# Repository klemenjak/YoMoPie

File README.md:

# Servus!

Computational methods for the enhancement of energy efficiency rely on a measurement process with sufficient accuracy and number of measurements. Networked energy meters, energy monitors, serve as a vital link between the energy consumption of households and key insights that reveal strategies to achieve significant energy savings.
With YoMoPie, we propose a user-oriented energy monitor for the Raspberry Pi platform that aims to enable intelligent energy services in households. YoMoPie measures active as well as apparent power, stores data locally, and integrates a user-friendly Python library. Furthermore, the presented energy monitor allows users to run self-designed services in their home to enhance energy efficiency. Potential services are (but not limited to) residential demand response, immediate user feedback, smart meter data analytics, or energy disaggregation.

<!--- YoMoPie builds on [the work published in [1]](https://link.springer.com/article/10.1007%2Fs00450-014-0290-8#/page-1).
YoMoPie provides the following advancements:

* It doesn't suffer from a data update rate of 1 second
* It stores data locally
* It integrates a new measurement IC that allows poly-phase metering
* It builds on the Raspberry platform
* The YoMoPie Python package enables easy handling -->

## Research Paper on YomoPie

All design files and pieces of software are available free of charge. However, in case you use the PCB design, code, or other material for research purposes, we kindly ask you to cite our peer-reviewed research paper:

* *Title*: YoMoPie: A User-Oriented Energy Monitor to Enhance Energy Efficiency in Households
* *Authors*: Mr. Christoph Klemenjak, Mr. Stefan Jost and Dr. Wilfried Elmenreich
* *Conference*: 2018 IEEE Conference on Technologies for Sustainability (SusTech)

Recommended Citation:
```
@INPROCEEDINGS{klemenjak2018yomopie,
author={C. Klemenjak and S. Jost and W. Elmenreich},
booktitle={2018 IEEE Conference on Technologies for Sustainability (SusTech)},
title={Yo{M}o{P}ie: {A} User-Oriented Energy Monitor to Enhance Energy Efficiency in Households},
year={2018},
volume={},
number={},
pages={},
keywords={},
doi={},
ISSN={},
month={Nov}}
```

|                 | YoMoPie  |
| ------------- | -----:|
|Communication|  WiFi, Ethernet, RF |
|Measurement|  P, Q, S, I, U |
|Number of connections| 1 or 3 |
|Integrated relay |  yes |
|Sampling frequency|  tba. |
|Data update rate |  tba. |
|Power calculation|  Hardware |
|Open-Source|  yes |
|RaspberryPi-compatible|  yes  |
|Costs| approx. 50€  |

Beside a current and a voltage sensor, the board integrates an energy metering chip, the ADE7754. Our library is designed in a way to offer single-phase as well as multi-phase metering.

## Installation

The YoMoPie Python package is available on Python Package Index (PyPI), a repository of software for the Python programming language, and can be installed by issuing one command:

```python
pip3 install YoMoPie
```
Additionally, the entire source code and a manual can be obtained from our YoMoPie Github repository.

## Examples of use

After a successful installation process, the YoMoPie package is available system-wide and can be accessed by a simple import command:
```python
import YoMoPie as yomopie
yp = yomopie.YoMoPie()
```

During initialisation, the number of line conductors has to be set (single or polyphase metering):
```python
yomo.set_lines(1)
```

To test the operation, we recommend to call the function *do_n_measurements*. Based on the number of samples and the sampling period, the function will return first measurement values and saves it into the target file:
```python
yomo.do_n_measurements(number of samples, sampling period, target file)
```

Active power, apparent power, current, and voltage samples can be read with commands such as:
```python
[t, I] = yp.get_irms()
[t, U] = yp.get_vrms()
[t, P] = yp.get_active_energy()
[t, S] = yp.get_apparent_energy()
```
In the same vein, users can activate continuous data logging or perform a fixed amount of subsequent measurements:
```python
yp.do_metering()
yp.do_n_measurements(quantity, rate, file)
```

The operational mode (OPMODE) register defines the general configuration of the integrated measurement chip ADE7754. By writing to this register, A/D converters can be turned on/off, sleep mode can be activated, or a software chip reset can be triggered. For further information, we refer to the datasheet of the measurement chip.

```python
yp.set_operational_mode(OPMODE)
```

# YoMoPie Python package documentation
**[Imports](#imports)**<br>
**[Classvariables](#classvariables)**<br>
**[Methods](#methods)**<br>
*[-init](#init)*<br>
*[-init_yomopie](#init_yomopie)*<br>
*[-set_lines](#set_lines)*<br>
*[-enable_board](#enable_board)*<br>
*[-disable_board](#disable_board)*<br>
*[-chip_reset](#chip_reset)*<br>
*[-write_8bit](#write_8bit)*<br>
*[-read_8bit](#read_8bit)*<br>
*[-write_16bit](#write_16bit)*<br>
*[-read_16bit](#read_16bit)*<br>
*[-read_24bit](#read_24bit)*<br>
*[-get_temp](#get_temp)*<br>
*[-get_laenergy](#get_laenergy)*<br>
*[-get_lappenergy](#get_lappenergy)*<br>
*[-get_period](#get_period)*<br>
*[-set_operational_mode](#set_operational_mode)*<br>
*[-set_measurement_mode](#set_measurement_mode)*<br>
*[-close_SPI_connection](#close_SPI_connection)*<br>
*[-get_aenergy](#get_aenergy)*<br>
*[-get_active_energy](#get_active_energy)*<br>
*[-get_apparent_energy](#get_apparent_energy)*<br>
*[-get_sample](#get_sample)*<br>
*[-get_sampleperperiod](#get_sampleperperiod)*<br>
*[-get_vrms](#get_vrms)*<br>
*[-get_irms](#get_irms)*<br>
*[-do_n_measurements](#do_n_measurements)*<br>
*[-do_metering](#do_metering)*<br>
*[-change_factors](#change_factors)*<br>
*[-reset_factors](#reset_factors)*<br>
*[-init_nrf24](#init_nrf24)*<br>
*[-write_nrf24](#write_nrf24)*<br>
*[-read_nrf24](#read_nrf24)*<br>
**[OPMODE](#opmode)**<br>
**[MMODE](#mmode)**<br>

## Imports
YomoPie requires some additional libraries:

**time**: The time package is required to obtain timestamps.

**math**: YoMoPie requires the math lib for calculations such as reactive energy.

**spidev**: The YoMoPie integrates an energy monitor IC, which communicates via SPI to the RPi. To enable this communication, YoMoPie exploits the spidev lib.

**sys**: This module provides access to some variables used or maintained by the interpreter and to functions that interact strongly with the interpreter.

**RPi.GPIO**: In order to allow further extensions of the YoMoPie eco-system, our package integrates the RPi.GPIO. Also, the reset pin is controlled via GPIO.

**NRF24**: This package allows to utilize the RF module for 2.4 GHz communication.

```python
import time
import math
import spidev
import sys
import RPi.GPIO as GPIO
from lib_nrf24 import NRF24
```
## Class variables

To correctly access the internal registers of the energy monitor IC, several custom variables are required to adjust the register values.

* **read** and **write**: These variables hold the mask that defines the operational mode. Therefore, for reading a register the given address and the **read** variable are the inputs of a bitwise AND operation. On the other hand, for writing to a register the register address and the **write** variable are the inputs of a bitwise OR operation.

* **spi**, **active_lines** and **debug**: These variables hold the SPI object, save the number of active lines, and enable/disable the debug mode.

* **radio**: This object will be used for the RF communication and its functions.
* **sample interval** and **max_f_sample**: defines the time between two samples (with respect to the start_sampling method) in seconds and the maximum sampling frequency (with respect to the sampling error).
* **active_power_LSB**, **apparent_power_LSB**, **vrms_factor** and **irms_factor**: Convert register values to physical quantities and represent permanent conversion factors.

```python
read = 0b00111111
write = 0b10000000
spi=0
radio=0
active_lines = 1
debug = 1

sample_intervall = 1
max_f_sample = 10

active_power_LSB= 0.000013292
apparent_power_LSB= 0.00001024
vrms_factor = 0.000047159
irms_factor = 0.000010807
```

## Methods

In this Section, we describe every method of our  package. A description of function parameters and return values is given.

### __init__

**Description**: This method represents  the constructor and creates a new YoMoPie object.

**Parameters**: None.

**Returns**: Nothing.

```python
def __init__(self):
	self.spi=spidev.SpiDev()
	self.init_yomopie()
	return
```

### init_yomopie

**Description**: Initialises the YoMoPie object. Sets the GPIO mode, disables GPIO warnings and defines pin 19 as output. Also opens a new SPI connection via the SPI device (0,0), sets the SPI speed to 62500 Hz and sets the SPI mode to 1. Finally, the function set_lines is called to set the MMODE, WATMODE and VAMODE.

**Parameters**: None.

**Returns**: Nothing.

```python
def init_yomopie(self):
	GPIO.setmode(GPIO.BCM)
	GPIO.setwarnings(False)
	GPIO.setup(19,GPIO.OUT)
	self.spi.open(0,0)
	self.spi.max_speed_hz = 62500
	self.spi.mode = 0b01
	self.set_lines(self.active_lines)
	self.sampleintervall = 1
	return
```

### set_lines

**Description**: This function sets the number of active phases that will be measured.

**Parameters**:
* lines - Number of phases

**Returns**: Nothing.

```python
def set_lines(self, lines):
	if (lines != 1) and (lines != 3):
		print("Incompatible number of power lines")
		return
	else:
		self.active_lines = lines
		if self.active_lines == 3:
			self.write_8bit(0x0D, 0x3F)
			self.write_8bit(0x0E, 0x3F)
			self.set_measurement_mode(0x70)
		elif self.active_lines == 1:
			self.write_8bit(0x0E, 0x24)
			self.set_measurement_mode(0x10)
			self.write_8bit(0x0D, 0x24)
		return
```

### enable_board

**Description**: Enables the board by pulling pin 19 to HIGH.

**Parameters**: None.

**Returns**: Nothing.

```python
def enable_board(self):
	GPIO.output(19, GPIO.HIGH)
	return
```

### disable_board

**Description**: Disables the board by pulling pin 19 to LOW.

**Parameters**: None.

**Returns**: Nothing.

```python
def disable_board(self):
	GPIO.output(19, GPIO.LOW)
	return
```

### chip_reset

**Description**: Resets the chip to the manufacturer settings

**Parameters**: None.

**Returns**: Nothing.

```python
def chip_reset(self):
	self.write_8bit(0x0A, 0x40)
	time.sleep(1);
	return
```		
### write_8bit    

**Description**: Writes 8 bit to the given address.

**Parameters**:

* register - 8 bit address of the register (see ADE7754 register table)

* value - 8 bit of value that will be written into the register

**Returns**: Nothing.

```python
def write_8bit(self, register, value):
	self.enable_board()
	register = register | self.write
	self.spi.xfer2([register, value])
	return
```

### read_8bit

**Description**: Reads 8 bit of data from the given address.

**Parameters**:
* register - 8 bit address of the register (see ADE7754 register table)

**Returns**: the 8 bit of data in the register as decimal

```python
def read_8bit(self, register):
	self.enable_board()
	register = register & self.read
	result = self.spi.xfer2([register, 0x00])[1:]        
	return result[0]
```

### write_16bit

**Description**: Writes 16 bit to the given address.

**Parameters**:

* register - 8 bit address of the register (see ADE7754 register table)

* value - 16 bit of value that will be written into the register

**Returns**: Nothing.

```python
def write_16bit(self, register, value):
	self.enable_board()
	register = register | self.write
	self.spi.xfer2([register, value[0], value[1]])
	return
```		

### read_16bit  

**Description**: Reads 16 bit of data from the given address.

**Parameters**:
* register - 8 bit address of the register (see ADE7754 register table)

**Returns**: the 16 bit of data in the register as decimal

```python
def read_16bit(self, register):
	self.enable_board()
	register = register & self.read
	result = self.spi.xfer2([register, 0x00, 0x00])[1:]
	dec_result = (result[0]<<8)+result[1]
	return dec_result
```

### read_24bit        

**Description**: Reads 24 bit of data from the given address.

**Parameters**:
* register - 8 bit address of the register (see ADE7754 register table)

**Returns**: the 24 bit of data in the register as decimal

```python
def read_24bit(self, register):
	self.enable_board()
	register = register & self.read
	result = self.spi.xfer2([register, 0x00, 0x00, 0x00])[1:]
	dec_result = (result[0]<<16)+(result[1]<<8)+(result[2])
	return dec_result
```

### get_temp

**Description**: Reads the temperature register (0x08).

**Parameters**: None.

**Returns**: A list [timestamp, temperature in °C]

```python
def get_temp(self):
	reg = self.read_8bit(0x08)
	temp = [time.time(),(reg-129)/4]
	return temp
```

### get_laenergy

**Description**: Reads the active energy register (0x03).

**Parameters**: None.

**Returns**: A list [timestamp, value of the register]

```python
def get_laenergy(self):
	laenergy = [time.time(), self.read_24bit(0x03)]
	return laenergy
```

### get_lappenergy

**Description**: Reads the apparent energy register (0x06).

**Parameters**: None.

**Returns**: A list [timestamp, value of the register]

```python
def get_lappenergy(self):
	lappenergy = [time.time(), self.read_24bit(0x06)]
	return lappenergy
```

### get_period   

**Description**: Reads the period register (0x07).

**Parameters**: None.

**Returns**: A list [timestamp, value of the register]

```python
def get_period(self):
       period = [time.time(), self.read_16bit(0x07)]
       return period
```

### set_operational_mode

**Description**: Sets the OPMODE. For more information see section OPMODE.

**Parameters**:
* value - 8 bit of data representing the OPMODE

**Returns**: Nothing.

```python
def set_operational_mode(self, value):
	self.write_8bit(0x0A, value)
	return
```

### set_measurement_mode

**Description**: Sets the MMODE. For more information see section MMODE.

**Parameters**:
* value - 8 bit of data representing the MMODE

**Returns**: Nothing.

```python
def set_measurement_mode(self, value):
	self.write_8bit(0x0B, value)
	return
```

### close_SPI_connection

**Description**: Closes the SPI connection.

**Parameters**: None.

Returns**: 0 if connection is closed.

```python
def close_SPI_connection(self):
	self.spi.close()
	return 0
```
### get_aenergy

**Description**: Reads the active energy register (0x01).

**Parameters**: None.

**Returns**: A list [timestamp, value of register converted to real value]

```python
def get_aenergy(self):
	aenergy = [time.time(), self.active_power_LSB * self.read_24bit(0x01) *  3600/self.sample_intervall]
	return aenergy
```
### get_active_energy

**Description**: Reads the active energy register (0x02) and resets the register value.

**Parameters**: None.

**Returns**: A list [timestamp, value of register converted to real value]

```python
def get_active_energy(self):
	aenergy =  [time.time(), self.active_power_LSB * self.read_24bit(0x02) *  3600/self.sample_intervall]
	return aenergy
```
### get_apparent_energy

**Description**: Reads the apparent energy register (0x05) and resets the register vlaue.

**Parameters**: None.

**Returns**: A list [timestamp, value of register converted to real value]

```python
def get_apparent_energy(self):
	appenergy = [time.time(), self.apparent_power_LSB * self.read_24bit(0x05)*  3600/self.sample_intervall]
	return appenergy
```
### get_sample

**Description**: Takes one sample and calculates the active energy, apparent energy, reactive energy, VRMS and IRMS.

**Parameters**: None.

**Returns**: A list of 7 elements [timestamp, active energy, apparent energy, reactive energy, period, VRMS, IRMS]

```python
def get_sample(self):
	aenergy = self.get_aenergy()[1] *self.active_factor
	appenergy = self.get_appenergy()[1] *self.apparent_factor
	renergy = math.sqrt(appenergy*appenergy - aenergy*aenergy)
	if self.debug:
		print"Active energy: %f W, Apparent energy: %f VA, Reactive Energy: %f var" %(aenergy, appenergy, renergy)
		print"VRMS: %f IRMS: %f" %(self.get_vrms()[1]*self.vrms_factor,self.get_irms()[1]*self.irms_factor)
	sample = []
	sample.append(time.time())
	sample.append(aenergy)
	sample.append(appenergy)
	sample.append(renergy)
	sample.append(self.get_period()[1])
	sample.append(self.get_vrms()[1]*self.vrms_factor)
	sample.append(self.get_irms()[1]*self.irms_factor)
	return sample
```

### get_vrms

**Description**: Reads the VRMS register depending.

**Parameters**: None.

**Returns**: A list of 2 elements [timestamp, Phase A VRMS] or 4 elements [timestamp, Phase A VRMS, Phase B VRMS, Phase C VRMS]

```python
def get_vrms(self):
	if self.active_lines == 1:
		avrms = [time.time(), self.read_24bit(0x2C)]
		return avrms
	elif self.active_lines == 3:
		vrms = []
		vrms.append(time.time())
		vrms.append(self.read_24bit(0x2C))
		vrms.append(self.read_24bit(0x2D))
		vrms.append(self.read_24bit(0x2E))
		return vrms
	return 0
```

### get_irms

**Description**: Reads the IRMS register.

**Parameters**: None.

**Returns**: A list of 2 elements [timestamp, Phase A IRMS] or 4 elements [timestamp, Phase A IRMS, Phase B IRMS, Phase C IRMS]

```python
def get_irms(self):
	if self.active_lines == 1:
		airms = [time.time(), self.read_24bit(0x29)]
		return airms
	elif self.active_lines == 3:
		irms = []
		irms.append(time.time())
		irms.append(self.read_24bit(0x29))
		irms.append(self.read_24bit(0x2A))
		irms.append(self.read_24bit(0x2B))
		return vrms
	return 0
```

### get_sampleperperiod

**Description**: Reads multiple register and returns the values adjusted to the sampling frequency. This function will be used in the do_n_measurements
 function.

**Parameters**:
* samplerate - the actual samplerate

**Returns**: A list of 7 elements [timestamp, active energy, apparent energy, reactive energy, period, VRMS, IRMS]

```python
def get_sampleperperiod(self, samplerate):
	aenergy = self.get_aenergy()[1] *self.active_factor * 3600/samplerate
	appenergy = self.get_appenergy()[1] *self.apparent_factor * 3600/samplerate
	renergy = math.sqrt(abs(appenergy*appenergy - aenergy*aenergy))
	vrms = self.get_vrms()[1]*self.vrms_factor
	irms = self.get_irms()[1]*self.irms_factor
	if self.debug:
		print("Active energy: %f W, Apparent energy: %f VA, Reactive Energy: %f var" % (aenergy, appenergy, renergy))
		print("VRMS: %f IRMS: %f" %(vrms,irms))
	sample = []
	sample.append(time.time())
	sample.append(aenergy)
	sample.append(appenergy)
	sample.append(renergy)
	sample.append(self.get_period()[1])
	sample.append(vrms)
	sample.append(irms)
	return sample
```

### do_n_measurements

**Description**: Takes *nr_samples* with sampling period *samplerate* and saves the measurements into the give file.

**Parameters**:

* nr_samples - this are the number of samples that will be taken, integer greater then 0
* samplerate - this is the time between each sample, integer greater then 0
* file - this will be the path and name of the file, where the date will be stored

**Returns**: A list of samples (each sample is a list of 7 elements)

```python
def do_n_measurements(self, nr_samples, samplerate, file):
	if (samplerate<1) or (nr_samples<1):
		return 0
	self.sample_intervall = samplerate
	samples = []
	for i in range(0, nr_samples):
		for j in range(0, samplerate):
			time.sleep(1)
	sample = self.get_sampleperperiod(samplerate)
	samples.append(sample)
	logfile = open(file, "a")
	for value in sample:
		logfile.write("%s; " % value)
	logfile.write("\n")
	logfile.close()
	return samples
```

### do_metering

**Description**: Starts a sampling process and saves the data into a file.

**Parameters**:

* f_sample - the sampling frequency (<= 10, but if max_f_sample is changed, this value can be up to 100 with a higher error)
* file - this will be the path and name of the file, where the date will be stored. If this parameter is empty the data will be stored in "smart_meter_output.csv".

**Returns**: Nothing.

```python
def do_metering(self, f_sample, file):
	if (f_sample > max_f_sample):
		print('Incompatible sampling frequency!')
		return 1
	if (file == ''):
		file = 'smart_meter_output.csv'
	for i in range(0,86400):
		sample = []
		sample.append(time.time())
		sample.append(i)
		sample.append(self.get_active_energy())
		sample.append(self.get_apparent_energy())
		data_file = open(file,'a')
		for value in sample:
			logfile.write("%s; " % value)
		logfile.write("\n")
		##print(sample)
		time.sleep(1/f_sample);
	return 0
```

### change_factors

**Description**: Changes the multiplication factors for the register values.

**Parameters**:

* active_f - this is the factor for the active energy calculation
* apparent_f - this is the factor for the apparent energy calculation
* vrms_f - this is the factor for the vrms calculation
* irms_f  this is the factor for the irms calculation

**Returns**: Nothing.

```python
def change_factors(self, active_f, apparent_f, vrms_f, irms_f):
	self.active_power_LSB = active_f
	self.apparent_power_LSB = apparent_f
	self.vrms_factor = vrms_f
	self.irms_factor = irms_f
	return
```

### reset_factors

**Description**: Resets the multiplication factors to the default values. The default values are calculated by our measurements with calibrated equipment.

**Parameters**: None.

**Returns**: Nothing.

```python
def reset_factors(self):
	self.active_power_LSB= 0.000013292
	self.apparent_power_LSB= 0.00001024
	self.vrms_factor = 0.000047159
	self.irms_factor = 0.000010807
	return
```

### init_nrf24

**Description**: Initializes the RF communication via the NRF24 chip.

**Parameters**: None.

**Returns**: Nothing.

```python
def init_nrf24(self):
	pipes = [[0xe7, 0xe7, 0xe7, 0xe7, 0xe7], [0xc2, 0xc2, 0xc2, 0xc2, 0xc2]]

	self.radio = NRF24(GPIO, self.spi)
	self.radio.begin(1, 13)
	self.radio.setPayloadSize(32)
	self.radio.setChannel(0x60)

	self.radio.setDataRate(NRF24.BR_2MBPS)
	self.radio.setPALevel(NRF24.PA_MIN)
	self.radio.setAutoAck(True)
	self.radio.enableDynamicPayloads()
	self.radio.enableAckPayload()
	self.radio.openWritingPipe(pipes[1])
	self.radio.openReadingPipe(1, pipes[0])
	self.radio.printDetails()
	return
```

### write_nrf24

**Description**: Sends a message via the RF communication.

**Parameters**:
* command - the message that will be written via RF

**Returns**: Nothing.

```python
def write_nrf24(self, command):
	message = []
	message = list(command)
	self.radio.write(message)
	print("Send: {}".format(message))

	if self.radio.isAckPayloadAvailable():
		pl_buffer = []
		self.radio.read(pl_buffer, self.radio.getDynamicPayloadSize())
		print(pl_buffer)
		print("Translating the acknowledgment to unicode chars...")
		string = ""
		for n in pl_buffer:
			if(n >= 32 and n <= 126):
			string += chr(n)
		print(string)
	return
```

### read_nrf24

**Description**: Reads a message via the RF communication.

**Parameters**: None.

**Returns**: Nothing.

```python
def read_nrf24(self):
	print("Ready to receive data...")
	self.radio.startListening()
	pipe = [0]
	while not self.radio.available(pipe):
		time.sleep(1/100)
	receivedMessage = []
	self.radio.read(receivedMessage, self.radio.getDynamicPayloadSize())

	print("Translating the receivedMessage to unicode chars...")
	string = ""
	for n in receivedMessage:
		if (n >= 32 and n <= 126):
			string += chr(n)
		print("Our sensor sent us: {}".format(string))
	self.radio.stopListening()
	return
```
## OPMODE
The operational mode (OPMODE) register defines the general configuration of the ADE7754 chip. For detailed information about the individual bits of this register we refer to [Table IX](https://github.com/klemenjak/YoMoPie/blob/master/Datasheets/ADE7754.pdf).

## MMODE
The configuration of period and peak measurements are defined by writing to the MMODE register (0x0B). For more information about the register we refer to [Table XII](https://github.com/klemenjak/YoMoPie/blob/master/Datasheets/ADE7754.pdf).

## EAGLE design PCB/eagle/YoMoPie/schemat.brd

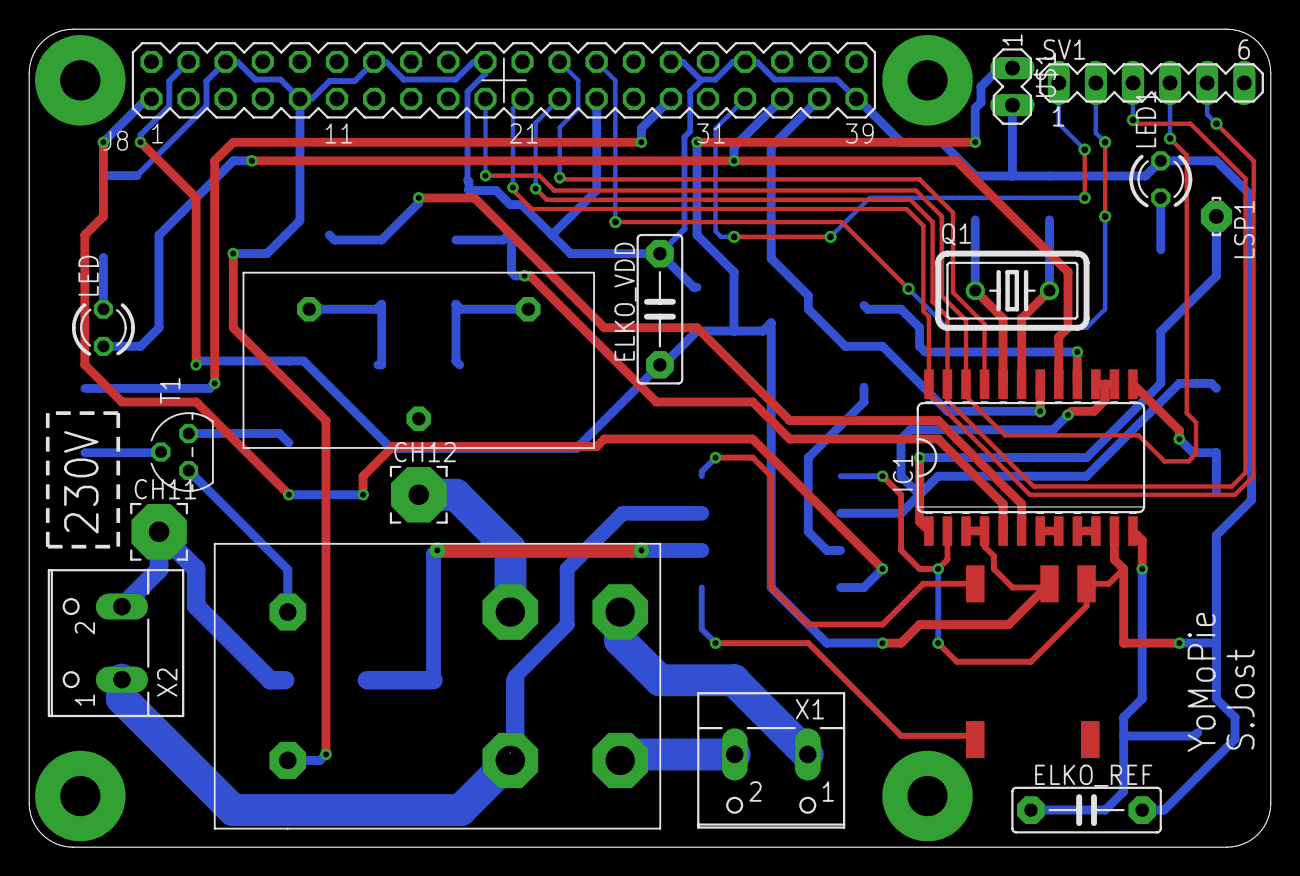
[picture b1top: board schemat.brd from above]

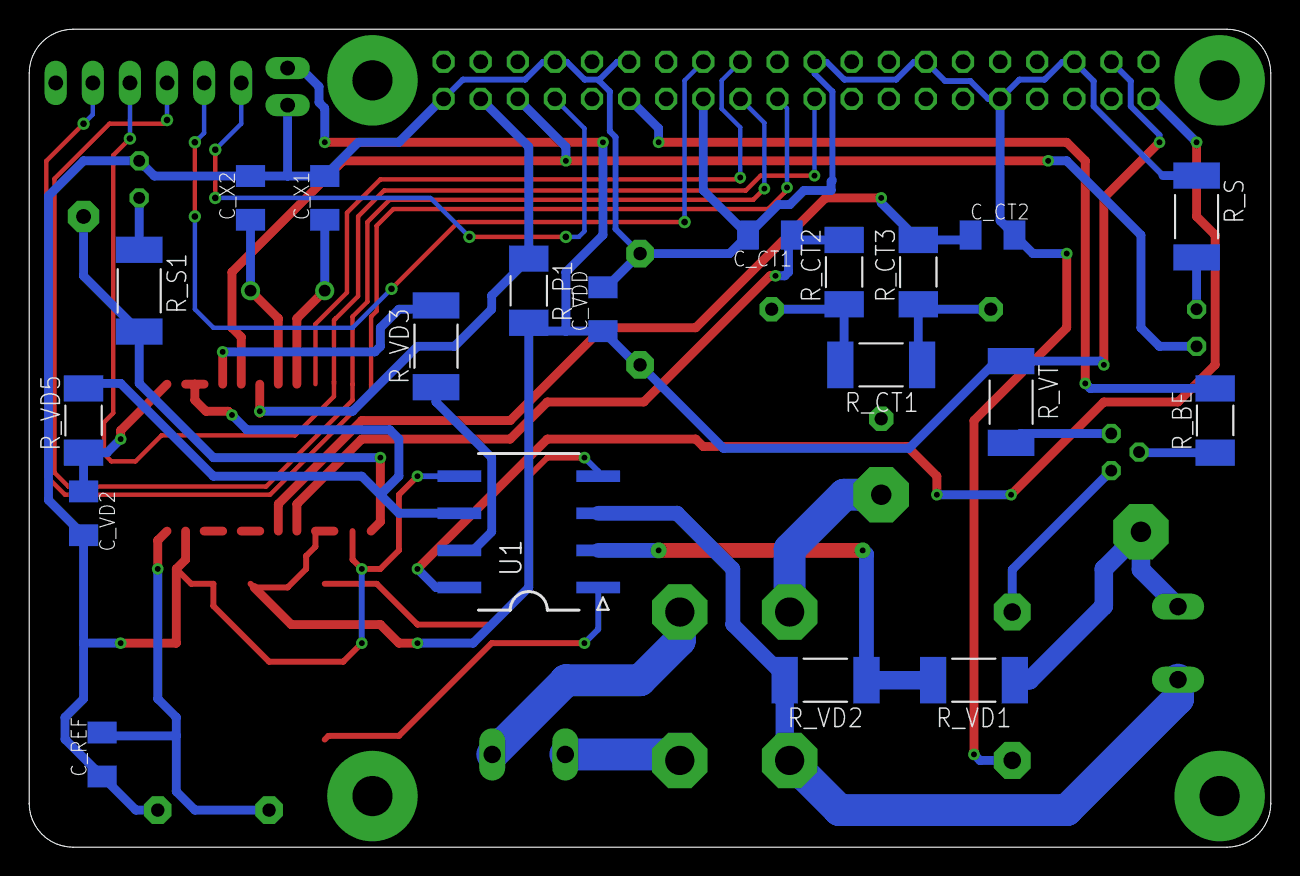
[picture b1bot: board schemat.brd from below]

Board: 2 copper layers, 85.0 x 56.0 mm, 38 parts (20 on the bottom side), 39 nets.

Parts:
CH11, CH12: WIREPAD3,81/1,4; 3,81/1,4
C_CT1, C_CT2: 33n; C1206K
C_REF: 100n; C1206K
C_VD2: 33n; C1206K
C_VDD: 100n; C1206K
C_X1, C_X2: 22p; C1206K
ELKO_REF: 10u; C7.5B3
ELKO_VDD: 10u; C7.5B3
IC1: ADE7754; SO24L
LED, LED1: LED3MM
LSP1: LSP10
PCB1: RASPBERRY_PI_B+_DIM; RASPBERRY_PI_BPLUS_DIM
Q1: HC18U-V
R_BE: 1k; R2010
R_CT1: 26; R2512
R_CT2, R_CT3: 1k; R2010
R_P1: 100k; R2010
R_S: 2k2; R2512
R_S1: 825; R2512
R_VD1: 1M; R2512
R_VD2: 810; R2512
R_VD3: 5k6; R2512
R_VD5: 1k; R2010
R_VT: 20; R2512
SV1: MA06-1
T1: 2N3904; TO92
U1: AMC1100DUB; DIP8-GULLWING
U$1: 2-PINHEAD
U$2: CST-1020; CST1020
U$3: TES1-0511; 0511
U$4: G4W-2212P-US-TV5
X1, X2: W237-102

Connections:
+3V3: PCB1.1, U1.8
+5V: C_VDD.1, ELKO_VDD.1, IC1.3, IC1.4, PCB1.4, R_P1.2, R_VT.1, U$1.1, U$3.+VIN
CE: PCB1.33, SV1.1
CS: IC1.21, PCB1.24
CSE: PCB1.26, SV1.2
DIN: IC1.22, PCB1.19, SV1.4
DOUT: IC1.24, PCB1.21, SV1.5
GND: C_CT1.2, C_CT2.2, C_REF.1, C_VD2.2, C_VDD.2, C_X1.2, C_X2.2, ELKO_REF.2, ELKO_VDD.2, IC1.2, IC1.11, LED1.K, PCB1.6, PCB1.9, PCB1.14, PCB1.20, PCB1.25, PCB1.30, PCB1.34, PCB1.39, R_S.1, U1.5, U$1.2, U$3.-VIN, U$4.6
IRQ: IC1.18, PCB1.37, R_P1.1
unnamed: C_REF.2, ELKO_REF.1, IC1.12
unnamed: U$4.1, X1.1
unnamed: C_VD2.1, IC1.13, R_VD5.1
unnamed: R_BE.1, T1.2
unnamed: U$4.2, X1.2
unnamed: CH12.1, U$4.3
unnamed: IC1.1, LSP1.MP, R_S1.2
unnamed: CH11.1, R_VD1.1, X2.2
unnamed: R_VT.2, T1.1
unnamed: LED1.A, R_S1.1
unnamed: T1.3, U$4.5
unnamed: R_VD1.2, R_VD2.1, U1.2
unnamed: IC1.7, IC1.8
unnamed: IC1.9, IC1.10
unnamed: R_CT1.2, R_CT2.1, U$2.1
unnamed: R_VD3.1, U1.7
unnamed: LED.K, R_S.2
unnamed: U1.1, U$3.+VOUT
unnamed: U1.4, U$3.-VOUT
unnamed: R_CT1.1, R_CT3.1, U$2.2
unnamed: C_CT2.1, IC1.6, R_CT3.2
unnamed: C_CT1.1, IC1.5, R_CT2.2
unnamed: C_X1.1, IC1.20, Q1.1
unnamed: C_X2.1, IC1.19, Q1.2
RELAY: PCB1.29, R_BE.2
RESET: IC1.17, LED.A, PCB1.35
SCLK: IC1.23, PCB1.23, SV1.3
V2N: IC1.14, IC1.15, R_VD5.2, U1.6
V2P: IC1.16, R_VD3.2
VSP: R_VD2.2, U1.3, U$4.4, X2.1

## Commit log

2017-11-26 Descritption
    updated project info
2017-11-26 Set theme jekyll-theme-cayman
2017-11-26 Set theme jekyll-theme-slate
2017-11-27 PCB_Pie
    added PCB data of the single-phase YoMoPie
2018-01-04 testcommit
2018-01-12 working spitest_ade7753.py
2018-01-12 working spitest_ade7754.py
2018-01-12 added file with some functions
2018-01-12 class yomopi and a class tester test_yomopi
2018-01-12 some minor changes
2018-01-12 fixed some bugs
2018-01-12 ready for testing
2018-02-11 added sampling and some other functions
2018-02-12 first sample test
2018-02-13 added timestamp
2018-02-13 nrf24 testing
2018-02-13 Added documentation for firmware
2018-02-13 fixed a bug
2018-02-14 library documentation examples addad and README.md updated
2018-02-14 README.md updated
2018-02-14 added table of content
2018-02-14 updated table of contents and fixed some code bugs
2018-02-14 updated table of contents
2018-02-16 description update
2018-02-16 Update on description
    Edited ReadMe file and fixed errors
2018-02-25 added some functions, updated some functions and updated readme
2018-03-09 added the nrf24 library and some functions for nrf write and read
2018-03-11 some changes
2018-03-15 calibration file updated
2018-03-15 added simulated calibration
2018-03-15 simulations and testing the error
2018-03-16 simulations
2018-03-16 Final calibration version
2018-03-16 calibration finished
2018-03-16 ieee_v2
2018-03-16 cfnum sign error
2018-03-16 hertzschmerz
2018-03-18 deleted testfile
2018-03-27 eagle board figure
2018-04-05 testfiles
2018-04-18 ieee
2018-04-18 ieeev2
2018-04-18 rollback
2018-04-19 calibration file update and chip reset function
2018-04-20 ieeev3
2018-04-26 python 3
2018-05-01 markdown update
2018-05-09 pip upload
2018-05-09 tabs corrected!
2018-05-09 added empty init file
2018-05-10 added init and some changes
2018-06-20 measurement test 1
2018-06-20 10 min meas
2018-08-31 summary
2018-08-31 bibtex
2018-08-31 bibfinal
2018-08-31 update on project description
